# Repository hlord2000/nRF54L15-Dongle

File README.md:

# Hardware Design with the nRF54L15 is Easy: Making an nRF54L15 Dongle in KiCad

TODO: add flash part, explain firmware bringup on board, get some made 

Everyone knows the nRF52840 dongle! It's an excellent way to prototype with BLE, USB, or Nordic's proprietary protocols ("Enhanced ShockBurst", "Gazelle"). As solid as the dongle is, it's time to add new features and creature comforts to the foundation it gave us. 

First, a short comparison of the nRF54L15 and the nRF52840. Why make the leap to the nRF54L15?
- The nRF54L15 is based on a modern 22nm process, showing a 2x performance increase and half of the power consumption of the nRF52840.
- The nRF54L15 has expanded non-volatile memory as compared to the nRF52840 with 1.5MB onboard (+512KB).
- The nRF54L15 has a peripheral RISC-V core (cool!) which has a lot of interesting uses. It can be used as another core running Zephyr RTOS or as a software defined peripheral with libraries we provide!
- A new 4mbps PHY is available (this supports proprietary protocols only at time of writing).
- New security features are available in the nRF54L15 including a key management unit (KMU), TrustZone, side channel attack detection, and hardware tamper detectors.

How do you perfect perfection? What does an nRF54L15 dongle look like? Any tradeoffs? Here are some things to consider:
- The nRF54L15 does not have a USB interface. We need some sort of chip between the L15 and host device. I propose that we use an nRF52833 to act as a UART bridge and add some extra functionality...
- As seen in the Thingy91 X, it is possible to create a CMSIS-DAP debugger with Zephyr! I'll connect the SWDCLK/SWDIO/RESET pins from the nRF54L15 to the nRF52833.
- Let's add some quality of life items: a STEMMA-QT/Qwiic connector and through holes with castellations.
- It is time for USB-C! We will use a USB-C plug so that it is a true dongle.
- For DFU purposes, we will include a small external flash part connected to the nRF54L15.
- We are not typically power limited with a dongle and do not need a connection to a battery. For more information on power consumption with the nRF54L15, check out the Online Power Profiler here: ##INCLUDE LINK##

We've defined our system, let's make a diagram:

I personally use KiCad for all hardware design I do. It's quite close to being an outright Altium replacement and the price (free) is hard to pass up. Check out my KiCad library for Nordic parts https://github.com/hlord2000/nordic-lib-kicad if you are also interested!

The nRF52833 can be powered directly from USB, but the nRF54L15 will need a 5V->3.3V regulator. Let's combine this with the USB-C plug and protection IC. 

Note the use of a 5.1k pull down resistor on the CC pin of the plug. This tells the upstream device, typically a computer, that this is a downstream device that can sink up to 500mA. If you were to need more power, consider using a dedicated USB power delivery (PD) PHY.

Let's move on to the nRF52833 debugger.

There is no need for an external 32.768KHz crystal oscillator since this design is not power constrained, so we'll use the internal RC oscillator. Any pins can be used for the peripherals on the nRF52833 and the SWD pins are bit-banged anyway, so I have connected them to the most convenient pins for routing to the nRF54L15. One small exception is the pins required to use the 32MHz high-speed SPI interface on the nRF52833 (which requires specific pins for full speed operation).

The nRF52833 debugger can itself be programmed through a Tag Connect TC2030 footprint. This saves a line on the BOM and seems to be quite common in industry. Tag Connect sells a cable that can connect to the debug out port on any Nordic devkit. The onboard debugger will also feature MCUBoot USB DFU if it becomes necessary to update firmware.

Now for the star of the show! I have added the nRF54L15 in QFN package, following the reference design available here (## INCLUDE LINK ##) to ensure correct passive component values. 

Some notes on the nRF54L15:

- Only GPIO ports 0 and 1 support GPIO interrupts! GPIO port #2 is intended for higher power/faster peripherals and does not have an associated GPIOTE peripheral. Please refer to the product specification for more info on peripheral power domains. Suffice it to say: port 0 is the lowest power port, port 1 is in between, and port 2 uses the most power. Use this when planning what peripheral instances or pins you plan to use.
- With the nRF54L15, certain peripherals require the use of "clock pins." My schematic symbol labels which are clock pins. Refer to the product spec for a complete list of what peripherals require clock pins (SPI SCK requires one among others).
- Some peripherals on GPIO port 2 have assigned pins. (I'm a broken record: refer to the product spec :D)
- The nRF54L15 has internal load capacitors for the high frequency (32MHz) and low frequency (32.768KHz) crystals. Nice to have! This reduces board area and BOM.

For IO, the nRF54L15 has a user button, reset button, addressable LED/NeoPixel, a STEMMA-QT port, and 2.54mm pin header holes with castellated edges.

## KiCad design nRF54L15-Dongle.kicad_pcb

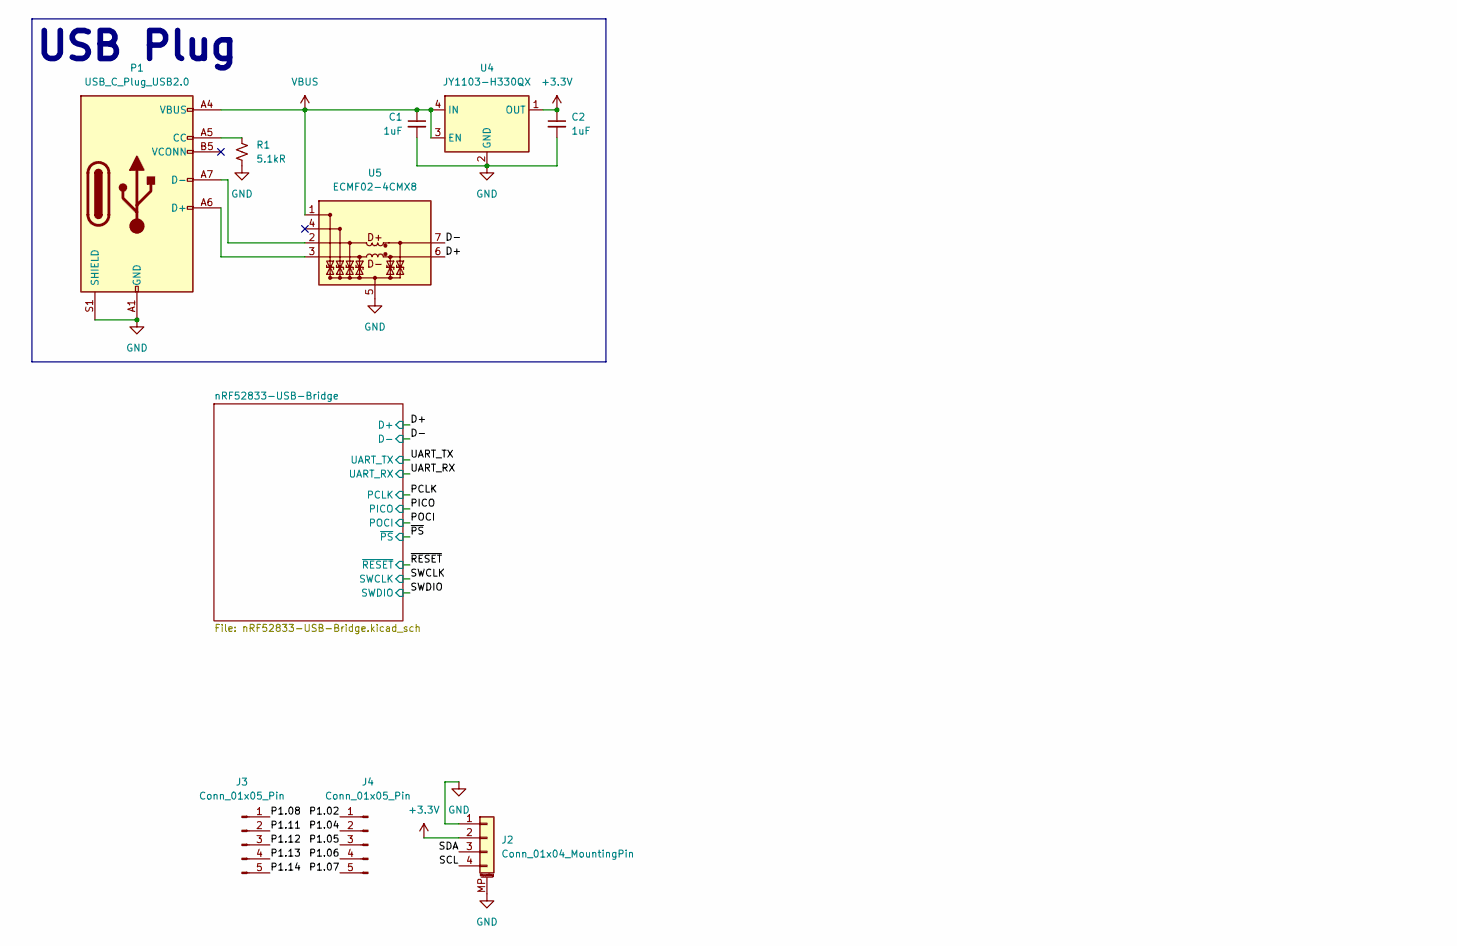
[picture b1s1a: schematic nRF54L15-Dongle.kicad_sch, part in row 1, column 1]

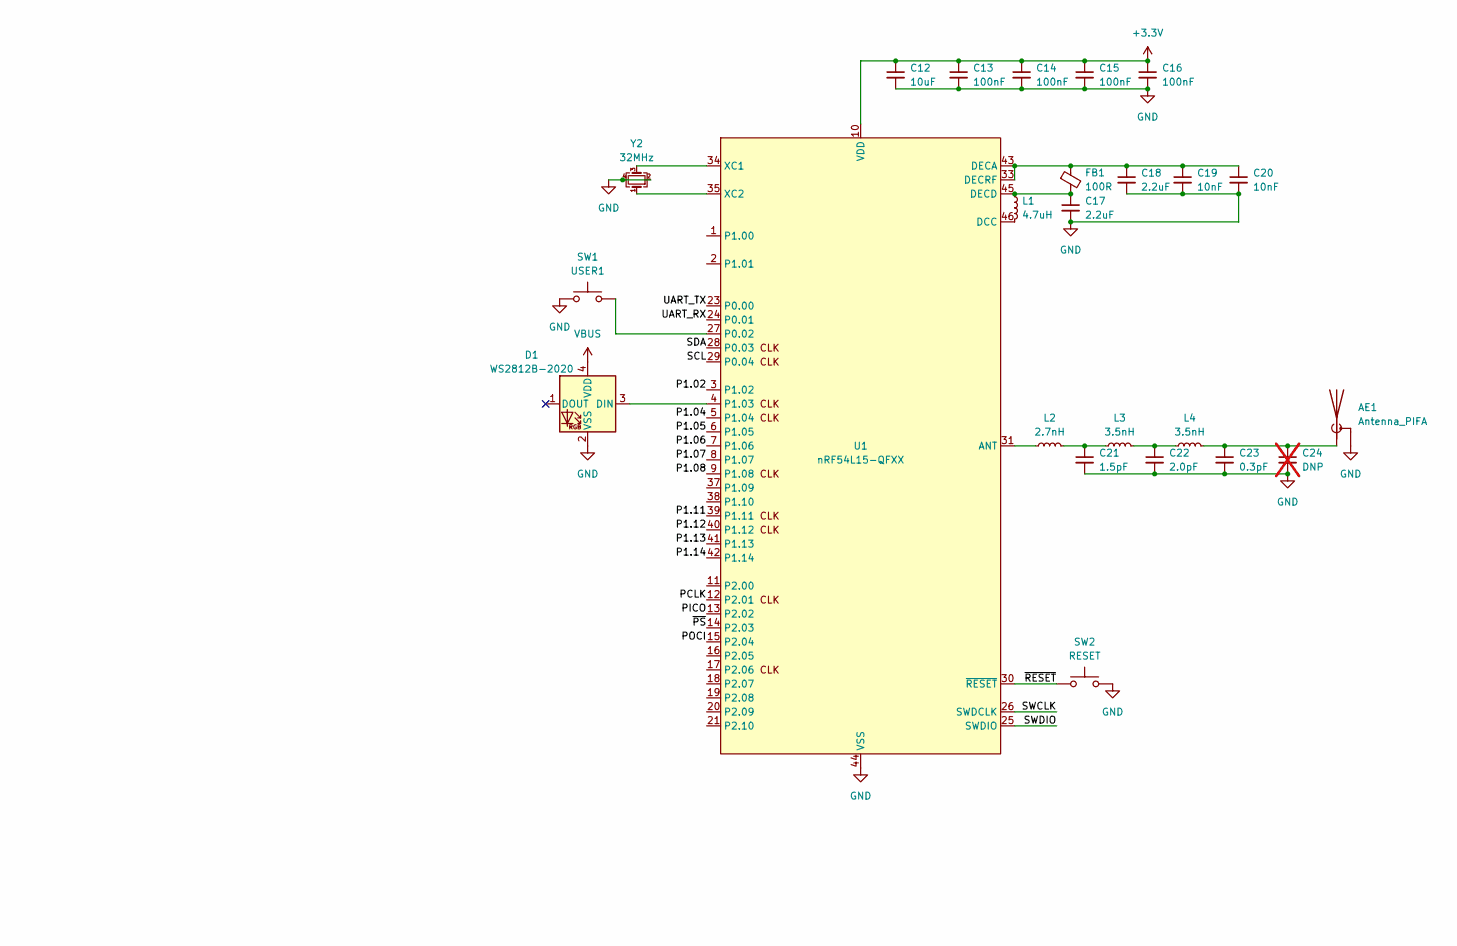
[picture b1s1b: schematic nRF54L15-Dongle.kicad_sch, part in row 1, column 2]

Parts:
AE1: Antenna_PIFA; Texas_SWRA117D_2.4GHz_Left
C1, C2: 1uF; C_0402_1005Metric
C12: 10uF; C_0402_1005Metric
C13, C14, C15, C16: 100nF; C_0402_1005Metric
C17, C18: 2.2uF; C_0402_1005Metric
C19, C20: 10nF; C_0402_1005Metric
C21: 1.5pF; C_0402_1005Metric
C22: 2.0pF; C_0402_1005Metric
C23: 0.3pF; C_0402_1005Metric
C24: DNP; C_0402_1005Metric; not fitted
D1: WS2812B-2020; LED_WS2812B-2020_PLCC4_2.0x2.0mm
FB1: 100R; L_0402_1005Metric
J2: Conn_01x04_MountingPin; JST_SH_SM04B-SRSS-TB_1x04-1MP_P1.00mm_Horizontal
J3, J4: Conn_01x05_Pin; PinHeader_1x05_P2.54mm_Vertical
L1: 4.7uH; L_0402_1005Metric
L2: 2.7nH; L_0402_1005Metric
L3, L4: 3.5nH; L_0402_1005Metric
P1: USB_C_Plug_USB2.0; USB_C_Plug_Molex_105444
R1: 5.1kR; R_0402_1005Metric
SW1: USER1; SW_Push_1P1T_NO_Vertical_Wuerth_434133025816
SW2: RESET; SW_Push_1P1T_NO_Vertical_Wuerth_434133025816
U1: nRF54L15-QFXX; QFN-48-1EP_6x6mm_P0.4mm_EP4.6x4.6mm_ThermalVias
U4: JY1103-H330QX; OnSemi_XDFN4-1EP_1.0x1.0mm_EP0.52x0.52mm; LCSC C3038104
U5: ECMF02-4CMX8; ST_UQFN-8L_1.2x2.5mm_P0.5mm
Y2: 32MHz; Crystal_SMD_2016-4Pin_2.0x1.6mm

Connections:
+3.3V: C2.1, C12.1, C13.1, C14.1, C15.1, C16.1, J2.2, U1.10 (VDD), U1.22 (VDD), U1.36 (VDD), U1.47 (VDD), U1.48 (VDD), U4.1 (OUT); also elsewhere on the board
/D+: U5.6 (D+_out); also elsewhere on the board
/D-: U5.7 (D-_out); also elsewhere on the board
/P1.02: J4.1, U1.3 (P1.02)
/P1.04: J4.2, U1.5 (P1.04)
/P1.05: J4.3, U1.6 (P1.05)
/P1.06: J4.4, U1.7 (P1.06)
/P1.07: J4.5, U1.8 (P1.07)
/P1.08: J3.1, U1.9 (P1.08)
/P1.11: J3.2, U1.39 (P1.11)
/P1.12: J3.3, U1.40 (P1.12)
/P1.13: J3.4, U1.41 (P1.13)
/P1.14: J3.5, U1.42 (P1.14)
/PCLK: U1.12 (P2.01); also elsewhere on the board
/PICO: U1.13 (P2.02); also elsewhere on the board
/POCI: U1.15 (P2.04); also elsewhere on the board
/SCL: J2.4, U1.29 (P0.04)
/SDA: J2.3, U1.28 (P0.03)
/SWCLK: U1.26 (SWDCLK); also elsewhere on the board
/SWDIO: U1.25 (SWDIO); also elsewhere on the board
/UART_RX: U1.24 (P0.01); also elsewhere on the board
/UART_TX: U1.23 (P0.00); also elsewhere on the board
/~PS: U1.14 (P2.03); also elsewhere on the board
/~RESET: SW2.2, U1.30 (~RESET); also elsewhere on the board
GND: AE1.2 (Shield), C1.2, C2.2, C12.2, C13.2, C14.2, C15.2, C16.2, C17.2, C18.2, C19.2, C20.2, C21.2, C22.2, C23.2, C24.2, D1.2 (VSS), J2.1, J2.MP (MountPin), P1.A1 (GND), P1.A12 (GND), P1.B1 (GND), P1.B12 (GND), P1.S1 (SHIELD), R1.2, SW1.1, SW2.1, U1.32 (VSS_PA), U1.44 (VSS), U1.49 (VSS), U4.2 (GND), U4.5 (GND), U5.5 (GND), U5.8 (GND), Y2.2, Y2.4; also elsewhere on the board
unnamed: AE1.1 (A), C23.1, C24.1, L4.2
unnamed: C21.1, L2.2, L3.1
unnamed: C22.1, L3.2, L4.1
unnamed: D1.3 (DIN), U1.4 (P1.03)
unnamed: P1.A5 (CC), R1.1
unnamed: P1.A6 (D+), U5.3 (D+_in)
unnamed: P1.A7 (D-), U5.2 (D-_in)
unnamed: L2.1, U1.31 (ANT)
unnamed: L1.2, U1.46 (DCC)
unnamed: C18.1, C19.1, C20.1, FB1.1, U1.33 (DECRF), U1.43 (DECA)
unnamed: C17.1, FB1.2, L1.1, U1.45 (DECD)
unnamed: SW1.2, U1.27 (P0.02)
unnamed: U1.34 (XC1), Y2.3
unnamed: U1.35 (XC2), Y2.1
VBUS: C1.1, D1.4 (VDD), P1.A4 (VBUS), P1.A9 (VBUS), P1.B4 (VBUS), P1.B9 (VBUS), U4.3 (EN), U4.4 (IN), U5.1 (VBUS); also elsewhere on the board

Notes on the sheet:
USB Plug

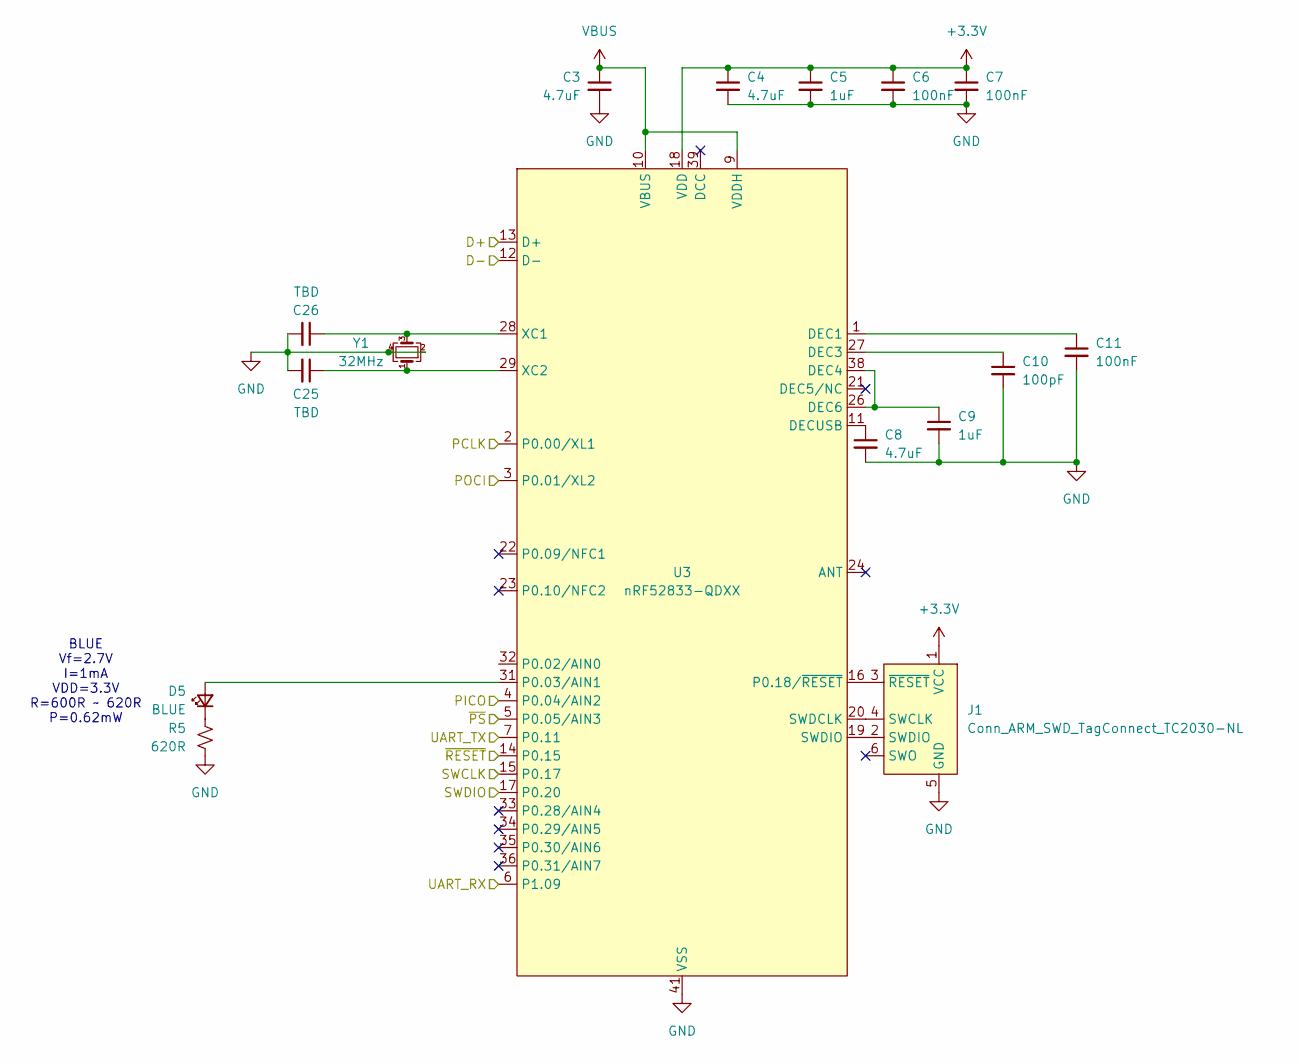
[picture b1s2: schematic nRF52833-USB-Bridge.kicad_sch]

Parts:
C3, C4, C8: 4.7uF; C_0402_1005Metric
C5, C9: 1uF; C_0402_1005Metric
C6, C7, C11: 100nF; C_0402_1005Metric
C10: 100pF; C_0402_1005Metric
C25, C26: TBD; C_0402_1005Metric
D5: BLUE; LED_0603_1608Metric; LCSC C7496819
J1: Conn_ARM_SWD_TagConnect_TC2030-NL; Tag-Connect_TC2030-IDC-NL_2x03_P1.27mm_Vertical
R5: 620R; R_0402_1005Metric
U3: nRF52833-QDXX; QFN-40-1EP_5x5mm_P0.4mm_EP3.6x3.6mm_ThermalVias
Y1: 32MHz; Crystal_SMD_2016-4Pin_2.0x1.6mm

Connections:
+3.3V: C4.1, C5.1, C6.1, C7.1, J1.1 (VCC), U3.8 (VDD), U3.18 (VDD), U3.30 (VDD), U3.40 (VDD); also elsewhere on the board
/D+: U3.13 (D+); also elsewhere on the board
/D-: U3.12 (D-); also elsewhere on the board
/PCLK: U3.2 (P0.00/XL1); also elsewhere on the board
/PICO: U3.4 (P0.04/AIN2); also elsewhere on the board
/POCI: U3.3 (P0.01/XL2); also elsewhere on the board
/SWCLK: U3.15 (P0.17); also elsewhere on the board
/SWDIO: U3.17 (P0.20); also elsewhere on the board
/UART_RX: U3.6 (P1.09); also elsewhere on the board
/UART_TX: U3.7 (P0.11); also elsewhere on the board
/~PS: U3.5 (P0.05/AIN3); also elsewhere on the board
/~RESET: U3.14 (P0.15); also elsewhere on the board
GND: C3.2, C4.2, C5.2, C6.2, C7.2, C8.2, C9.2, C10.2, C11.2, C25.2, C26.2, J1.5 (GND), R5.2, U3.25 (VSS_PA), U3.37 (VSS), U3.41 (VSS), Y1.2, Y1.4; also elsewhere on the board
unnamed: D5.2 (A), U3.31 (P0.03/AIN1)
unnamed: D5.1 (K), R5.1
unnamed: J1.4 (SWCLK), U3.20 (SWDCLK)
unnamed: J1.2 (SWDIO), U3.19 (SWDIO)
unnamed: J1.3 (~RESET), U3.16 (P0.18/~RESET)
unnamed: C11.1, U3.1 (DEC1)
unnamed: C10.1, U3.27 (DEC3)
unnamed: C9.1, U3.26 (DEC6), U3.38 (DEC4)
unnamed: C8.1, U3.11 (DECUSB)
unnamed: C26.1, U3.28 (XC1), Y1.3
unnamed: C25.1, U3.29 (XC2), Y1.1
VBUS: C3.1, U3.9 (VDDH), U3.10 (VBUS); also elsewhere on the board

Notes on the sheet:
BLUE Vf=2.7V I=1mA VDD=3.3V R=600R ~ 620R P=0.62mW

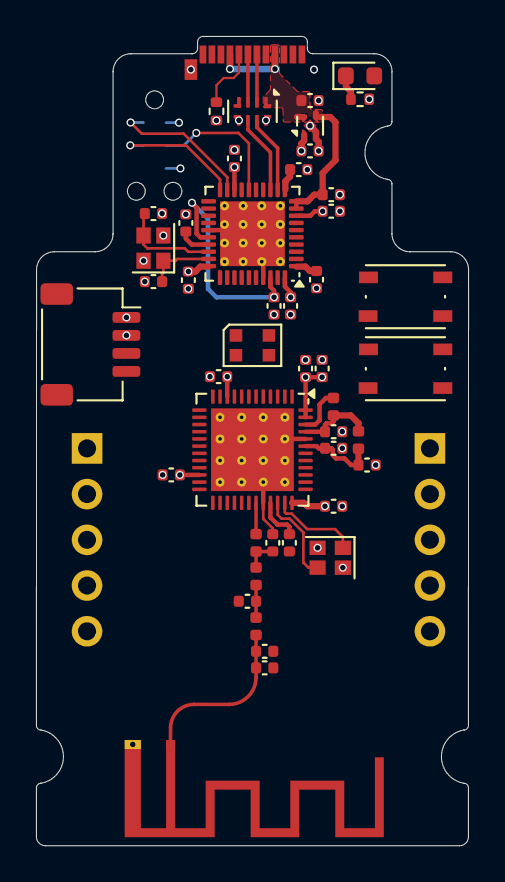
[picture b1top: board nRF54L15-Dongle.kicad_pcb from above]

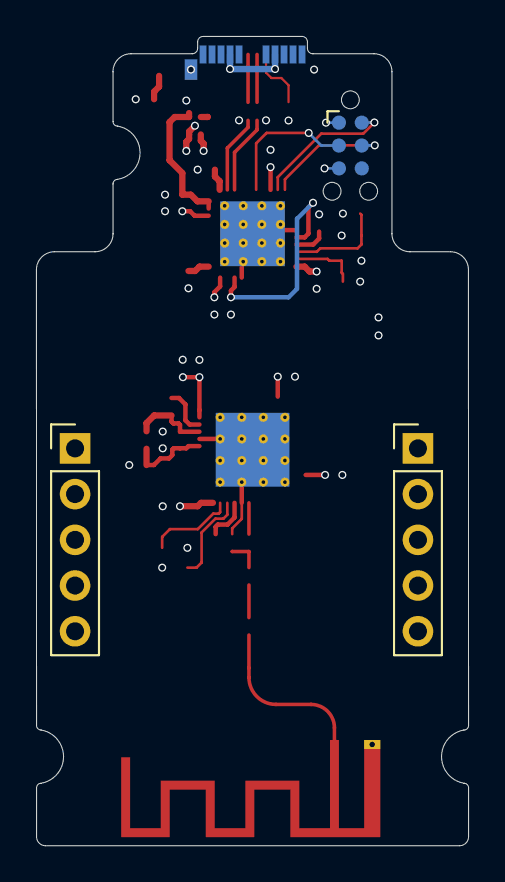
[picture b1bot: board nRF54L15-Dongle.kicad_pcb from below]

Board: 4 copper layers, 24.0 x 45.0 mm, 49 parts (3 on the bottom side), 49 nets.

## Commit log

2025-02-19 Initial commit.
